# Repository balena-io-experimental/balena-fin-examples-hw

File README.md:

# balena-fin-examples-hw
A collection of sample hardware designs for the balenaFin. This collection will be improved with more examples over time, make sure to check it out from time to time!

Example | Description | Compatible with | EDA/CAD Platform 
------------ | ------------ | ------------ | ------------ 
HAT Template | Template design to use as base for custom HATs for the balenaFin | v1.1 balenaFin | Altium/CircuitStudio/KiCAD

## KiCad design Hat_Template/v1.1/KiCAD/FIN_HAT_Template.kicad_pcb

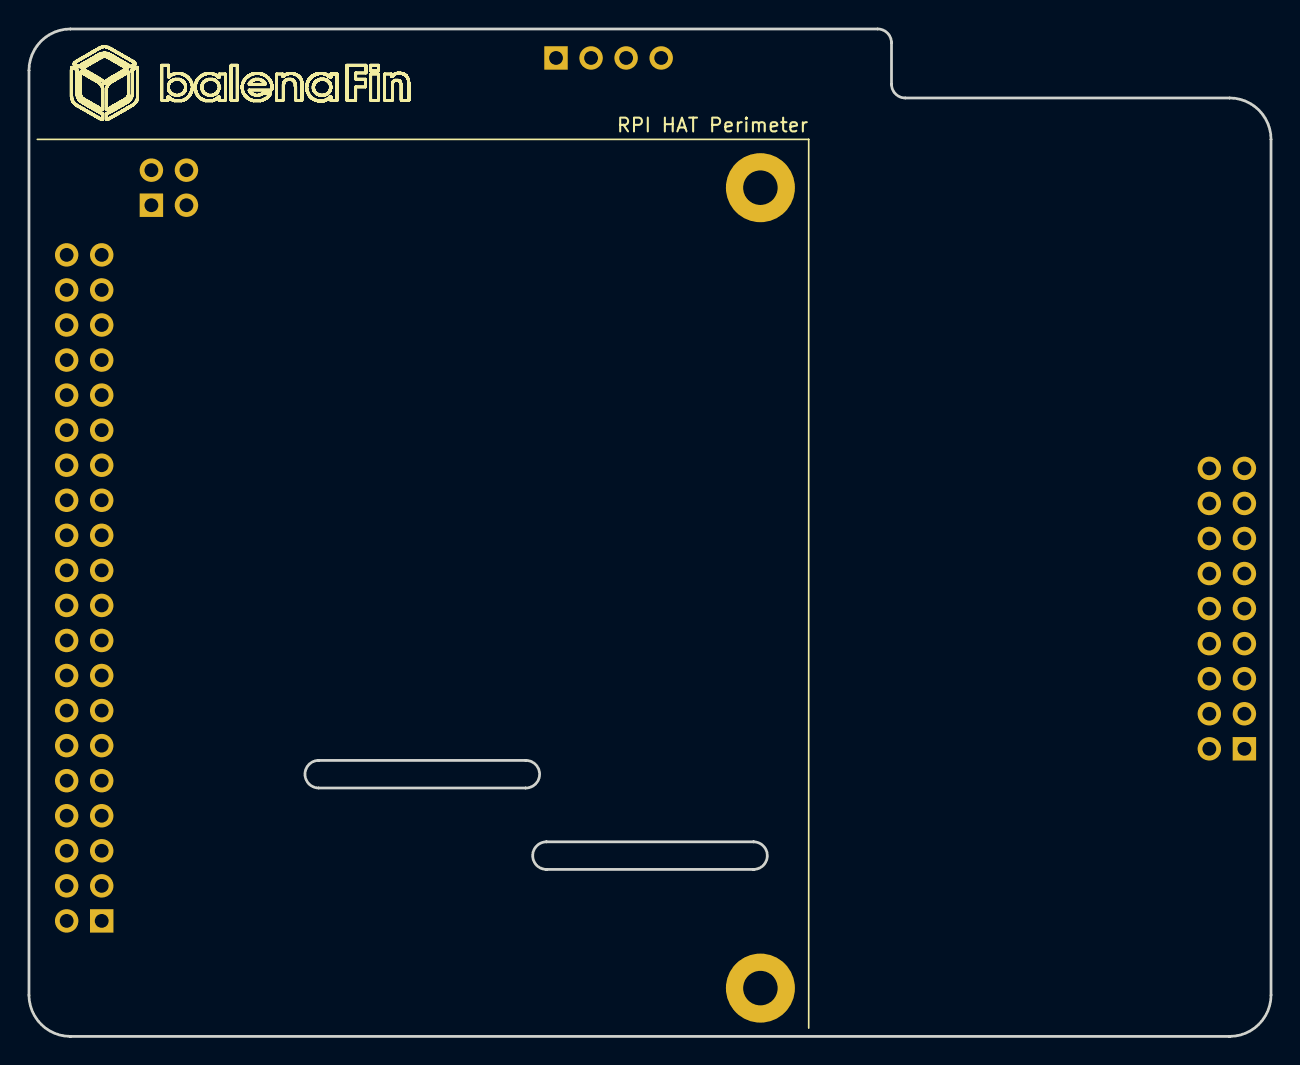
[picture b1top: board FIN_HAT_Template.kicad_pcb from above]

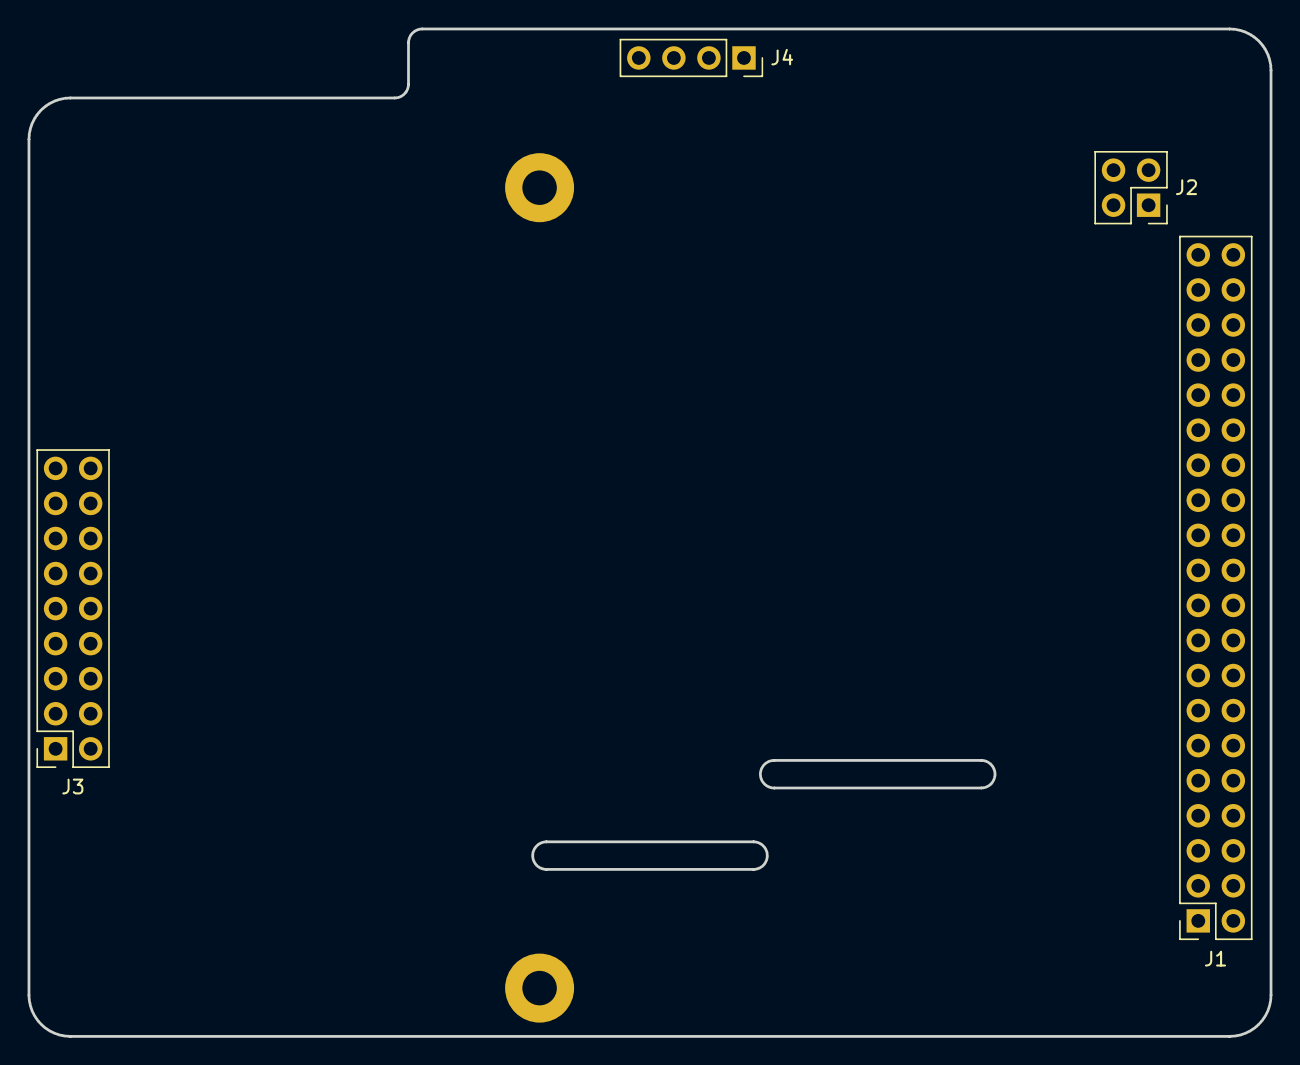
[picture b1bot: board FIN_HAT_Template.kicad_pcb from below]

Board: 2 copper layers, 90.0 x 73.0 mm, 6 parts (4 on the bottom side), 3 nets, no tracks yet.

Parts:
H1, H2: MountingHole_Pad; MountingHole_2.5mm_Pad
J1: Raspberry_Pi_2_3; PinSocket_2x20_P2.54mm_Vertical
J2: POE_Header; PinSocket_2x02_P2.54mm_Vertical
J3: Co-Processor_Header; PinSocket_2x09_P2.54mm_Vertical
J4: USB_Header; PinSocket_1x04_P2.54mm_Vertical

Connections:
+3V3: J1.1, J1.17
+5V: J1.2, J1.4, J4.1
GND: J1.6, J1.9, J1.14, J1.20, J1.25, J1.30, J1.34, J1.39, J3.17, J4.4

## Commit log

2019-06-06 Initial README
    Change-type: minor
2019-06-06 Added HAT template in Altium
    Change-type: major
2020-07-14 KiCAD Template 1st Commit
2020-07-15 Created a lib for our schematic symbols
2020-07-16 Created footrpints lib - Fixed the mirrored footprints issue - Added the dimenions
2020-07-16 Added a keepout area above the WiFi antenna in Top & Bottom layers
2020-07-16 Added a missing dimension.
2020-07-16 Update Readme file
2020-07-17 Solved the 3D models issue and converted the male pin headers to female sokets
2020-07-17 Fixed the orientaion of the POE header
2020-07-17 Modified the RaspberryPi Header to match the physical header pinout
2020-07-20 Adds meta data to KiCAD template
    Cleans up meta data for KiCAD template and organises file structure for projects.
    Change-type: minor
2020-07-21 Removes previous directory
    Hat_Template -> hat_template
    Change-type: minor
    <alexbucknall@balena.io>
2020-07-21 Update gitignore file
2020-07-21 Added KiCAD project files [it was missing due to a mistake in the previous gitignore file ]
2020-07-21 Added fp-lib-table and .sch-bak to the gitignore file
2020-07-21 Revert "Added fp-lib-table and .sch-bak to the gitignore file"
    This reverts commit 9285d22df39f05a9b5487f84e59e5ede12b040fb.
2020-07-21 Added fp-lib-table and .sch-bak to the gitignore file
    Change-type: minor
